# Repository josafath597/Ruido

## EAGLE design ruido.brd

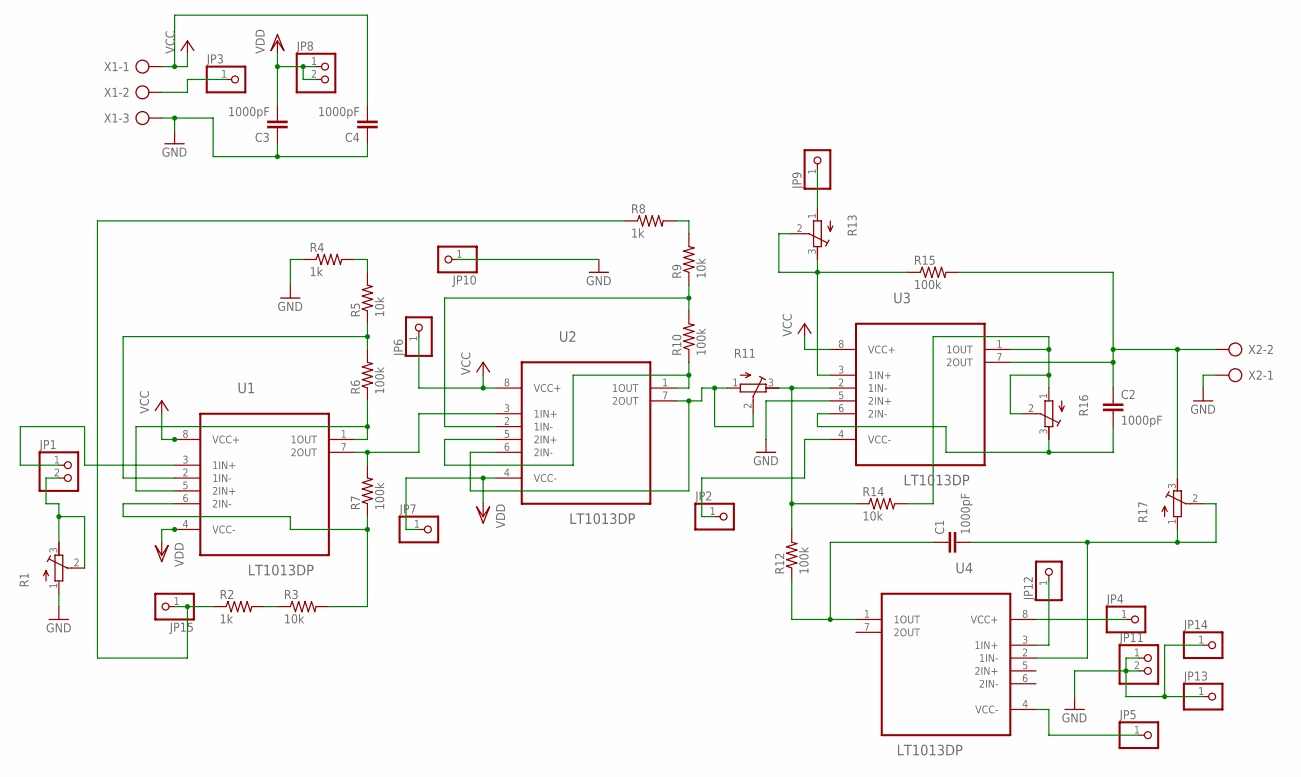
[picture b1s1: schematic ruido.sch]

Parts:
C1, C2, C3, C4: 1000pF; C050-024X044
JP1, JP8, JP11: PINHD-1X2; 1X02
JP2, JP3, JP4, JP5, JP6, JP7, JP9, JP10, JP12, JP13, JP14, JP15: PINHD-1X1; 1X01
R1, R11, R13, R16, R17: R-TRIMM3296W; RTRIM3296W
R2, R4, R8: 1k; 0207/10
R3, R5, R9, R14: 10k; 0207/10
R6, R7, R10, R12, R15: 100k; 0207/10
U1, U2, U3, U4: LT1013DP; DIP254P762X508-8
X1: AK500/3
X2: AK500/2

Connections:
GND: C3.1, C4.1, JP10.1, JP11.1, JP11.2, JP13.1, JP14.1, R1.1 (A), R4.1, U3.5 (2IN+), X1.3, X2.1
unnamed: R6.1, U1.1 (1OUT), U1.5 (2IN+)
unnamed: R5.1, R6.2, U1.2 (1IN-)
unnamed: R4.2, R5.2
unnamed: R7.2, U1.7 (2OUT), U2.3 (1IN+)
unnamed: R3.2, R7.1, U1.6 (2IN-)
unnamed: R2.2, R3.1
unnamed: R10.1, U2.1 (1OUT), U2.5 (2IN+)
unnamed: R9.1, R10.2, U2.2 (1IN-)
unnamed: R8.2, R9.2
unnamed: R13.2 (S), R13.3 (E), R15.1, U3.3 (1IN+)
unnamed: R11.1 (A), R11.2 (S), U2.6 (2IN-), U2.7 (2OUT)
unnamed: R14.2, R16.1 (A), R16.2 (S), U3.1 (1OUT)
unnamed: R11.3 (E), R12.2, R14.1, U3.2 (1IN-)
unnamed: C2.2, R16.3 (E), U3.6 (2IN-)
unnamed: C2.1, R15.2, R17.3 (E), U3.7 (2OUT), X2.2
unnamed: C1.1, R12.1, U4.1 (1OUT)
unnamed: C1.2, R17.1 (A), R17.2 (S), U4.2 (1IN-)
unnamed: JP1.2, R1.2 (S), R1.3 (E)
unnamed: JP1.1, U1.3 (1IN+)
unnamed: JP5.1, U4.4 (VCC-)
unnamed: JP4.1, U4.8 (VCC+)
unnamed: JP9.1, R13.1 (A)
unnamed: JP2.1, U3.4 (VCC-)
unnamed: JP3.1, X1.2
unnamed: JP12.1, U4.3 (1IN+)
unnamed: JP15.1, R2.1, R8.1
VCC: C4.2, JP6.1, U1.8 (VCC+), U2.8 (VCC+), U3.8 (VCC+), X1.1
VDD: C3.2, JP7.1, JP8.1, JP8.2, U1.4 (VCC-), U2.4 (VCC-)

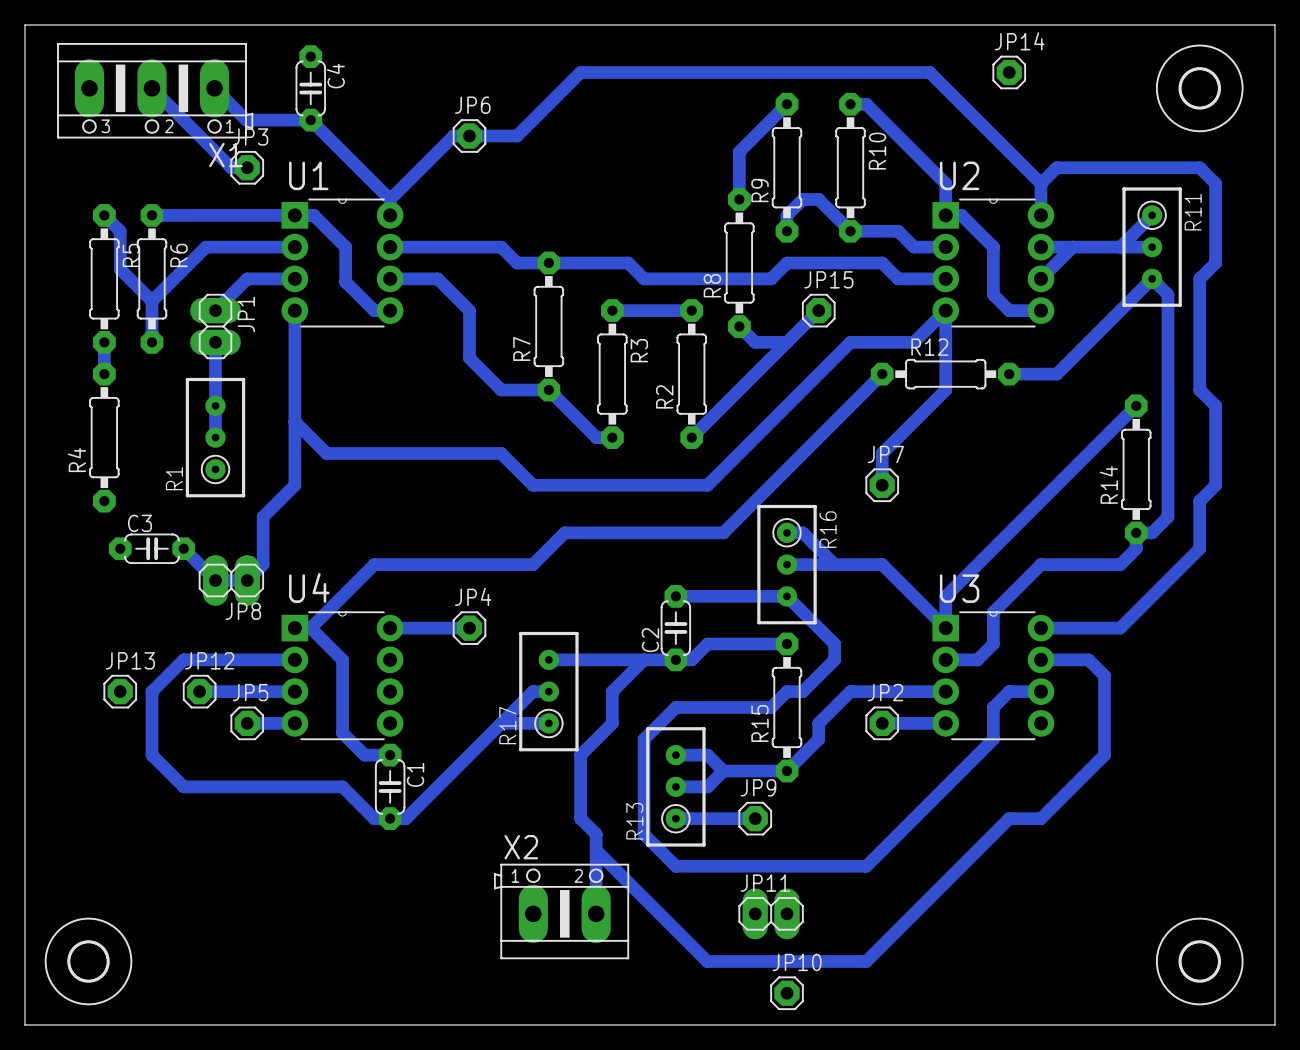
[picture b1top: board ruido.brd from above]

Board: 2 copper layers, 100.0 x 80.0 mm, 45 parts (0 on the bottom side), 29 nets.

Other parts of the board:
U$1, U$2, U$3: 3,0
